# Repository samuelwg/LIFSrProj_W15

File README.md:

**Repository for Senior Project ECEn 490 Section 5, Winter 2015 Semester, BYU**

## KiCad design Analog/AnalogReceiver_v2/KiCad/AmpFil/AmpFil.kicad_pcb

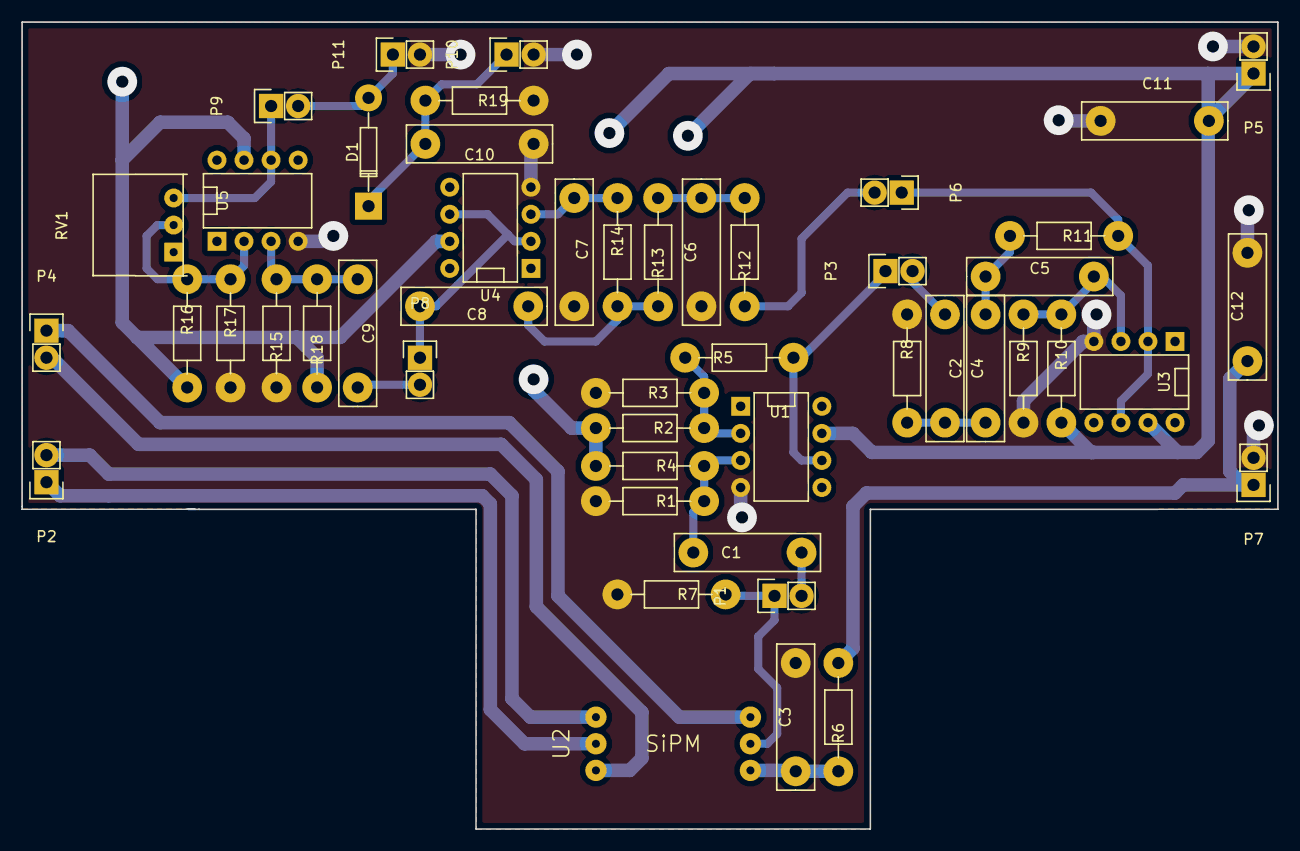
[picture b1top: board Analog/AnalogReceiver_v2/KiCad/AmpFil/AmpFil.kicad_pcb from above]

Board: 2 copper layers, 117.9 x 75.7 mm, 49 parts (0 on the bottom side), 29 nets.

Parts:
C1, C9: .2u; Cap_Horizontal_Shop
C2, C6: 22n; Cap_Horizontal_Shop
C3, C8: 10n; Cap_Horizontal_Shop
C4, C5: 33n; Cap_Horizontal_Shop
C7: 470p; Cap_Horizontal_Shop
C10: 15n; Cap_Horizontal_Shop
C11, C12: 150u; Cap_Horizontal_Shop
D1: DIODE; Diode_Shop
P1, P2, P3, P4, P5, P6, P7, P8, P9, P10, P11: CONN_01X02; Pin_Header_1x02_Shop
R1, R4, R14, R15, R18: 33k; Resistor_Horizontal_Shop
R2, R3, R16, R17: 1k; Resistor_Horizontal_Shop
R5: 12k; Resistor_Horizontal_Shop
R6: 5.6k; Resistor_Horizontal_Shop
R7: 22k; Resistor_Horizontal_Shop
R8: 4.7k; Resistor_Horizontal_Shop
R9, R10: 480k; Resistor_Horizontal_Shop
R11: 15k; Resistor_Horizontal_Shop
R12: 11k; Resistor_Horizontal_Shop
R13: 120k; Resistor_Horizontal_Shop
R19: 1meg; Resistor_Horizontal_Shop
RV1: 100-100k; Potentiometer_Shop
U1, U3, U4, U5: LT1677; DIP-8__300_Shop
U2: SiPM

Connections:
29.7V: C12.2, P7.1, R6.1
+3.3VP: C11.2, P5.1, R2.2, R4.1, R10.2, R16.2, R18.1, U1.7, U3.7, U4.7, U5.7
/A1: P3.1, R5.1, U1.6
/A2: P9.1, RV1.3, U5.6
/F1: P6.1, R11.1, U3.2, U3.6
/F2: C8.1, P8.1, U4.2, U4.6
GND: C3.1, C6.1, C7.1, C10.2, C11.1, C12.1, P5.2, P7.2, P10.2, P11.2, R1.1, R3.2, R7.2, R8.2, R9.2, R15.1, R17.2, R19.2, U1.4, U3.4, U4.4, U5.4
unnamed: C1.1, R1.2, R4.2, U1.3
unnamed: C1.2, P1.2
unnamed: C2.1, C4.2, R8.1
unnamed: C2.2, P3.2
unnamed: C3.2, R6.2, U2.6
unnamed: C4.1, C5.2, R11.2
unnamed: C5.1, R9.1, R10.1, U3.3
unnamed: C6.2, R12.1, R13.2
unnamed: C7.2, R14.1, U4.3
unnamed: C8.2, R13.1, R14.2
unnamed: C9.1, R15.2, R18.2, U5.3
unnamed: C9.2, P8.2
unnamed: P2.1, U2.2
unnamed: P2.2, U2.1
unnamed: P6.2, R12.2
unnamed: R2.1, R3.1, R5.2, U1.2
unnamed: R16.1, R17.1, RV1.2, U5.2
ThR+: P4.1, U2.4
ThR-: P4.2, U2.3
Vin: P1.1, R7.1, U2.5
Vout: D1.1, P9.2, P11.1
Voutp: C10.1, D1.2, P10.1, R19.1

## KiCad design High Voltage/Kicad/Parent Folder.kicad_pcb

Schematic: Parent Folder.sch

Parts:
C1, C2, C3, C4, C5, C6, C7, C8: C; C_1206_HandSoldering
Q1, Q2, Q3: STN0214
Q4: BUT11A; TO220_VERT
Q5: NPN; TO220_VERT
R1, R2, R3, R4, R5, R6, R7, R8, R9, R10, R11, R12, R13, R14, R15, R16, R17, R30: R; R_1206_HandSoldering
R18, R19, R20, R21, R22, R23, R24, R25, R26, R27, R28, R29: R; RES_1W
R31: Varable_Res; POT
TP1, TP2, TP3, TP4, TP5, TP6, TP7, TP8, TP9, TP10, TP11, TP12, TP13: Test_point; PINTST
U1, U2: OP275; OpAmp
U3: TEENSY3.1
U4: EMCO_F40

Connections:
+5V: R31.2; also elsewhere on the board
+12V: Q4.2 (C), U1.8 (V+), U2.8 (V+); also elsewhere on the board
-12V: U1.4 (V-), U2.4 (V-); also elsewhere on the board
GND: C1.2, C2.2, C3.2, C4.2, C5.2, C6.2, C7.2, C8.2, Q1.1 (E), Q2.1 (E), Q3.1 (E), R1.1, R2.1, R3.1, R4.1, R17.2, U3.1 (GND), U3.17 (GND), U4.2 ((-)In), U4.4 ((-)Out); also elsewhere on the board
unnamed: C1.1, R9.1, R13.2
unnamed: C2.1, R10.1, R14.2
unnamed: C3.1, R11.1, R15.2
unnamed: C4.1, R12.1, R16.2
unnamed: C5.1, Q1.3 (B), R13.1
unnamed: C6.1, Q2.3 (B), R14.1
unnamed: C7.1, Q3.3 (B), R15.1
unnamed: C8.1, Q4.1 (B), R16.1
unnamed: Q1.2 (C), Q1.4 (C), R18.2, R21.2, TP12.1
unnamed: Q2.2 (C), Q2.4 (C), R19.2, R22.2, TP9.1
unnamed: Q3.2 (C), Q3.4 (C), R20.2, R23.2, TP11.1
unnamed: Q4.3 (E), R17.1, TP5.1, U4.1 ((+)In)
unnamed: Q5.1, R30.1
unnamed: Q5.2, TP7.1
unnamed: Q5.3, R31.1
unnamed: R1.2, R5.2, U1.2 (-)
unnamed: R2.2, R6.2, U1.6 (-)
unnamed: R3.2, R7.2, U2.2 (-)
unnamed: R4.2, R8.2, U2.6 (-)
unnamed: R5.1, R9.2, TP1.1, U1.1
unnamed: R6.1, R10.2, TP2.1, U1.7
unnamed: R7.1, R11.2, TP3.1, U2.1
unnamed: R8.1, R12.2, TP4.1, U2.7
unnamed: R18.1, R24.2
unnamed: R19.1, R27.2
unnamed: R20.1, R29.2
unnamed: R21.1, R25.2
unnamed: R22.1, R26.2
unnamed: R23.1, R28.2
unnamed: R24.1, R25.1, R26.1, R27.1, R28.1, R29.1, U4.3 ((+)Out)
unnamed: R30.2, TP13.1
unnamed: TP6.1, U3.19 (DAC)
unnamed: TP8.1, U3.22 (P15)
unnamed: TP10.1, U3.21 (P14)
unnamed: U1.3 (+), U3.8 (P6)
unnamed: U1.5 (+), U3.7 (P5)
unnamed: U2.3 (+), U3.6 (P4)
unnamed: U2.5 (+), U3.5 (P3)

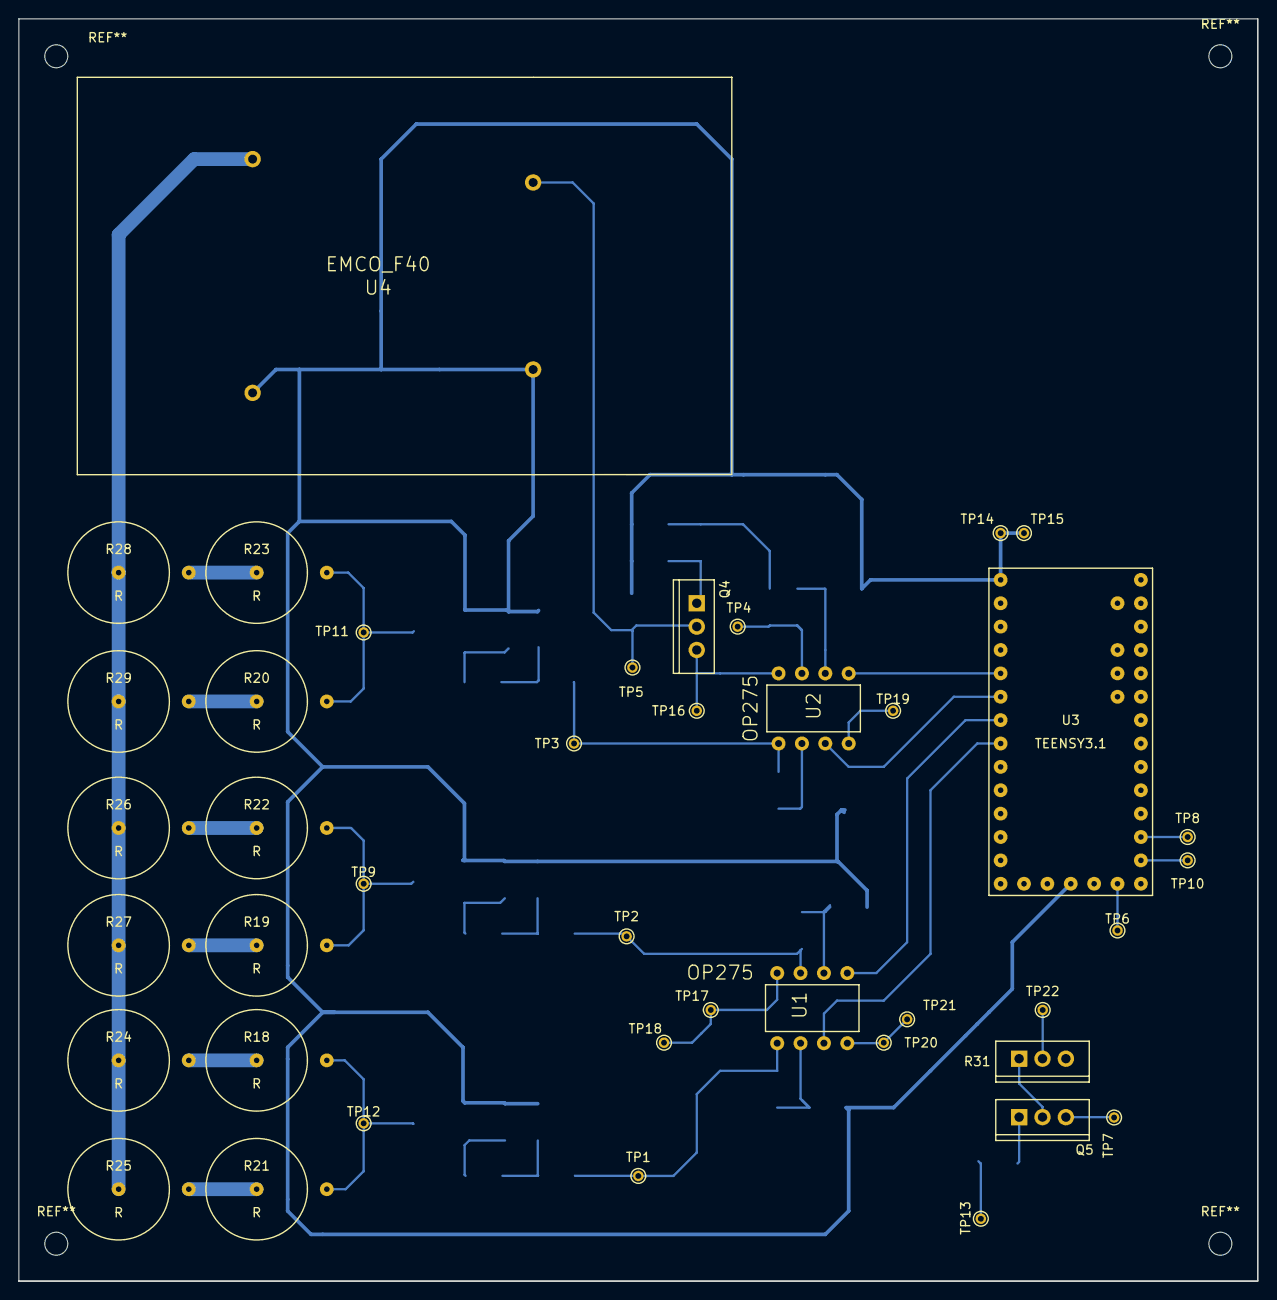
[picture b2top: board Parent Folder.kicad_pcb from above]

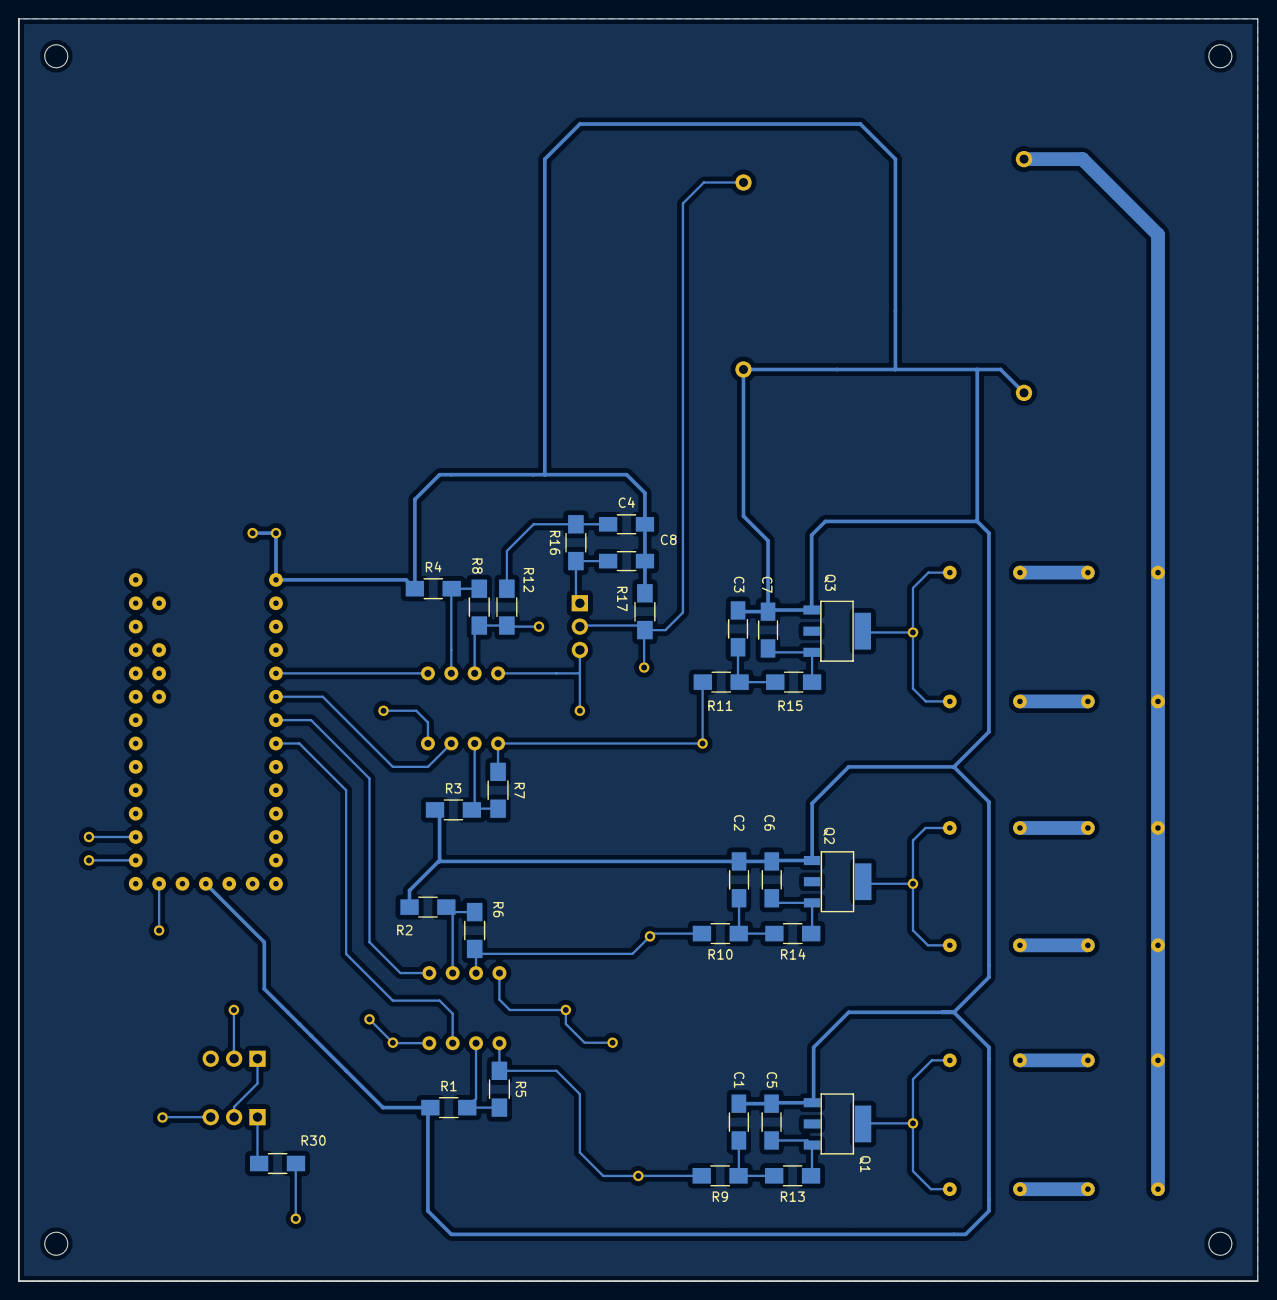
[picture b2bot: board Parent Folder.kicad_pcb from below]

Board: 2 copper layers, 134.6 x 137.2 mm, 70 parts (29 on the bottom side), 42 nets.

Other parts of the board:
TP14, TP15: GND; PINTST
TP16, TP17, TP18: +12V; PINTST
TP19, TP20, TP21: -12V; PINTST
TP22: +5V; PINTST

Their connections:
+5V: TP22.1; also elsewhere on the board
+12V: TP16.1, TP17.1, TP18.1; also elsewhere on the board
-12V: TP19.1, TP20.1, TP21.1; also elsewhere on the board
GND: TP14.1, TP15.1; also elsewhere on the board

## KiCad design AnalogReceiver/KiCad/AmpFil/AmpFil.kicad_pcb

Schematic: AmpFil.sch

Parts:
C1, C3: .2u; Capacitor13x4RM10
C2, C10: 10n; Capacitor13x4RM10
C4, C7: 22n; Capacitor13x4RM10
C5, C6: 33n; Capacitor13x4RM10
C8: 470p; Capacitor13x4RM10
C9: 15n; Capacitor13x4RM10
D1: DIODE; Diode_DO-35_SOD27_Horizontal_RM10
P1, P2, P3, P5: CONN_01X02; Pin_Header_Angled_2x01
P4: CONN_02X03; Pin_Header_Angled_2x03
P6, P7: CONN_01X02; Pin_Header_Angled_1x02
R1, R4, R8, R11, R19: 33k; Resistor_Horizontal_RM10mm
R2, R3, R9, R10: 1k; Resistor_Horizontal_RM10mm
R5: 100k; Resistor_Horizontal_RM10mm
R6: 5.6k; Resistor_Horizontal_RM10mm
R7: 22k; Resistor_Horizontal_RM10mm
R13: 4.7k; Resistor_Horizontal_RM10mm
R14, R15: 480k; Resistor_Horizontal_RM10mm
R16: 15k; Resistor_Horizontal_RM10mm
R17: 11k; Resistor_Horizontal_RM10mm
R18: 120k; Resistor_Horizontal_RM10mm
R20: 1meg; Resistor_Horizontal_RM10mm
RV1: 100-100k; Potentiometer_Trimmer-Suntan-TSR-3386C
U1: SiPM
U2, U3, U4, U5: LT1677; DIP-8__300

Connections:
29.7V: P4.6, R6.1
+3.3VP: P4.2, R2.2, R4.1, R9.2, R11.1, R15.2, U2.7 (+), U3.7 (+), U4.7 (+), U5.7 (+)
/A1: P2.1, R5.1, U2.6 (Vo)
/A2: P3.1, RV1.1, U3.6 (Vo)
/F1: P5.1, R16.1, U4.2 (-i), U4.6 (Vo)
GND: C2.1, C7.1, C8.1, C9.2, P4.1, P4.5, P6.2, P7.2, R1.1, R3.2, R7.2, R8.1, R10.2, R13.2, R14.2, R20.2, U2.4 (-), U3.4 (-), U4.4 (-), U5.4 (-)
unnamed: C1.1, R1.2, R4.2, U2.3 (+i)
unnamed: C2.2, R6.2, U1.6
unnamed: C3.1, R8.2, R11.2, U3.3 (+i)
unnamed: C3.2, P2.2
unnamed: C4.1, C5.2, R13.1
unnamed: C4.2, P3.2
unnamed: C5.1, C6.2, R16.2
unnamed: C6.1, R14.1, R15.1, U4.3 (+i)
unnamed: C7.2, R17.1, R18.2
unnamed: C8.2, R19.1, U5.3 (+i)
unnamed: C10.2, R18.1, R19.2
unnamed: P1.1, U1.2 (TE+)
unnamed: P1.2, U1.1 (TE-)
unnamed: P5.2, R17.2
unnamed: R2.1, R3.1, R5.2, U2.2 (-i)
unnamed: R9.1, R10.1, RV1.2, U3.2 (-i)
ThR+: P4.4, U1.4 (ThR)
ThR-: P4.3, U1.3 (ThR)
Vin: C1.2, R7.1, U1.5 (An(-))
Vout: C10.1, D1.1, P6.1, U5.2 (-i), U5.6 (Vo)
Voutp: C9.1, D1.2, P7.1, R20.1

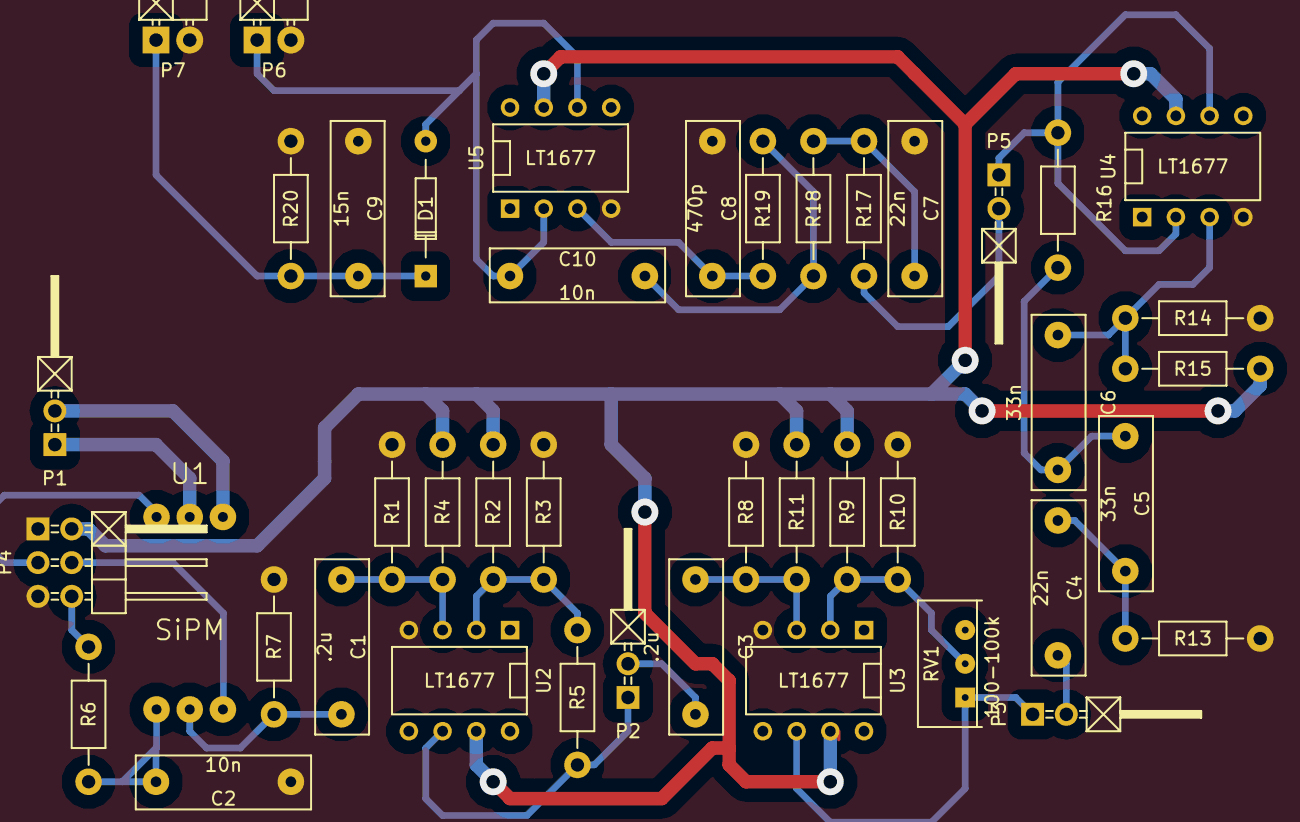
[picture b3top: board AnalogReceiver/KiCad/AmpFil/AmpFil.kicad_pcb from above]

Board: 2 copper layers, 43 parts (0 on the bottom side), 27 nets.

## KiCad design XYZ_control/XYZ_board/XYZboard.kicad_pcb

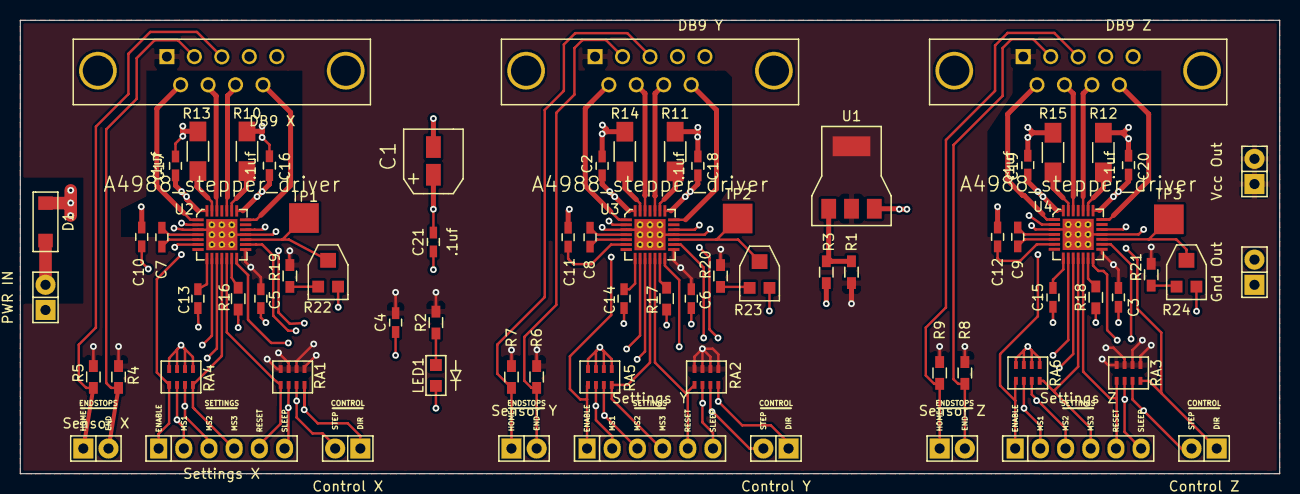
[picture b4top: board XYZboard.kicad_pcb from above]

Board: 4 copper layers, 127.0 x 45.7 mm, 75 parts (0 on the bottom side), 75 nets.

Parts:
C1: 47uF; PCE3929CT-ND
C2, C4, C5, C6, C7, C8, C9, C10, C11, C12, C16, C17, C18, C19, C20, C21: .1uf; C_0603_HandSoldering
C3: 1uF; C_0603_HandSoldering
C13, C14, C15: .22uF; C_0603_HandSoldering
D1: DIODE; SD2010S040S3R0
J1: DB9 X; DB9MD
J2: Control X; Pin_Header_Straight_1x02
J3: Control Y; Pin_Header_Straight_1x02
J4: Control Z; Pin_Header_Straight_1x02
J5: PWR IN; Pin_Header_Straight_1x02
J6: Settings X; Pin_Header_Straight_1x06
J7: Settings Y; Pin_Header_Straight_1x06
J8: Settings Z; Pin_Header_Straight_1x06
J9: Vcc Out; Pin_Header_Straight_1x02
J10: DB9 Y; DB9MD
J11: Gnd Out; Pin_Header_Straight_1x02
J12: Sensor X; Pin_Header_Straight_1x02
J13: Sensor Y; Pin_Header_Straight_1x02
J14: Sensor Z; Pin_Header_Straight_1x02
J15: DB9 Z; DB9MD
LED1: PWR LED; LGR971-KN-1
R1: 240; R_0603_HandSoldering
R2: 1k; R_0603_HandSoldering
R3, R4, R5, R6, R7, R8, R9: 715; R_0603_HandSoldering
R10, R11, R12, R13, R14, R15: .11; R_1206_HandSoldering
R16, R17, R18: 20k; R_0603_HandSoldering
R19, R20, R21: 2.49k; R_0603_HandSoldering
R22, R23, R24: 10k; TC33X-103ECT-ND
RA1, RA2, RA3, RA4, RA5, RA6: 20k; CAT16-203J4LFCT-ND
TP1, TP2, TP3: Test_point; Measurement_Point_Square-SMD-Pad_Big
U1: LM317MSTT3G_Voltage_Regulator; voltage_regulator_sot223
U2, U3, U4: A4988_stepper_driver; Qfn_28_A4988_with_thermal_vias

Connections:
GND: C1.2, C2.1, C3.1, C4.2, C5.2, C6.2, C13.1, C14.1, C15.1, C16.1, C17.1, C18.1, C19.1, C20.1, C21.1, J1.4, J5.1, J10.4, J11.1, J11.2, J15.4, LED1.2, R3.1, R10.1, R11.1, R12.1, R13.1, R14.1, R15.1, R16.1, R17.1, R18.1, R22.3, R23.3, R24.3, RA4.1, RA4.2, RA4.3, RA4.4, RA5.1, RA5.2, RA5.3, RA5.4, RA6.1, RA6.2, RA6.3, RA6.4, U2.3, U2.18, U2.29, U3.3, U3.18, U3.29, U4.3, U4.18, U4.29
unnamed: C7.1, U2.4
unnamed: C7.2, U2.5
unnamed: C8.1, U3.4
unnamed: C8.2, U3.5
unnamed: C9.1, U4.4
unnamed: C9.2, U4.5
unnamed: C10.2, U2.6
unnamed: C11.2, U3.6
unnamed: C12.2, U4.6
unnamed: C13.2, U2.8
unnamed: C14.2, U3.8
unnamed: C15.2, U4.8
unnamed: LED1.1, R2.1
unnamed: R1.1, R3.2, U1.1
unnamed: R10.2, U2.23
unnamed: R11.2, U3.23
unnamed: R12.2, U4.23
unnamed: R13.2, U2.27
unnamed: R14.2, U3.27
unnamed: R15.2, U4.27
unnamed: R16.2, U2.13
unnamed: R17.2, U3.13
unnamed: R18.2, U4.13
unnamed: R19.1, R22.1
unnamed: R20.1, R23.1
unnamed: R21.1, R24.1
PWR_IN: D1.1, J5.2
V+: C1.1, C2.2, C10.1, C11.1, C12.1, C16.2, C17.2, C18.2, C19.2, C20.2, C21.2, D1.2, U1.3, U2.22, U2.28, U3.22, U3.28, U4.22, U4.28
VCC: C3.2, C4.1, C5.1, C6.1, J1.1, J9.1, J9.2, J10.1, J15.1, R1.2, R2.2, R4.2, R5.2, R6.2, R7.2, R8.2, R9.2, R19.2, R20.2, R21.2, RA1.5, RA1.6, RA1.7, RA1.8, RA2.5, RA2.6, RA2.7, RA2.8, RA3.5, RA3.6, RA3.7, RA3.8, U1.2, U1.4, U2.15, U3.15, U4.15
dir1: J2.1, RA1.4, U2.19
dir2: J3.1, RA2.4, U3.19
dir3: J4.1, RA3.4, U4.19
enable1: J6.1, RA4.5, U2.2
enable2: J7.1, RA5.5, U3.2
enable3: J8.1, RA6.5, U4.2
ms1_1: J6.2, RA4.6, U2.9
ms1_2: J7.2, RA5.6, U3.9
ms1_3: J8.2, RA6.6, U4.9
ms2_1: J6.3, RA4.7, U2.10
ms2_2: J7.3, RA5.7, U3.10
ms2_3: J8.3, RA6.7, U4.10
ms3_1: J6.4, RA4.8, U2.11
ms3_2: J7.4, RA5.8, U3.11
ms3_3: J8.4, RA6.8, U4.11
out1a_1: J1.8, U2.24
out1a_2: J10.8, U3.24
out1a_3: J15.8, U4.24
out1b_1: J1.9, U2.21
out1b_2: J10.9, U3.21
out1b_3: J15.9, U4.21
out2a_1: J1.7, U2.26
out2a_2: J10.7, U3.26
out2a_3: J15.7, U4.26
out2b_1: J1.6, U2.1
out2b_2: J10.6, U3.1
out2b_3: J15.6, U4.1
ref1: R22.2, TP1.1, U2.17
ref2: R23.2, TP2.1, U3.17
ref3: R24.2, TP3.1, U4.17
reset1: J6.5, RA1.1, U2.12
reset2: J7.5, RA2.1, U3.12
reset3: J8.5, RA3.1, U4.12
sensor1_1: J1.2, J12.2, R4.1
sensor1_2: J10.2, J13.2, R6.1
sensor1_3: J14.2, J15.2, R8.1
sensor2_1: J1.3, J12.1, R5.1
sensor2_2: J10.3, J13.1, R7.1
sensor2_3: J14.1, J15.3, R9.1
sleep1: J6.6, RA1.2, U2.14
sleep2: J7.6, RA2.2, U3.14
sleep3: J8.6, RA3.2, U4.14
step1: J2.2, RA1.3, U2.16
step2: J3.2, RA2.3, U3.16
step3: J4.2, RA3.3, U4.16

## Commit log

2015-01-22 adding XYZ control code
2015-01-26 Adding XYZ motor control board design
2015-01-27 Updated motor control board
    Added pull up resistors for the hall effect sensors
2015-01-27 updated motor control footprints
2015-01-27 Worked on python interface for XYZ
2015-01-27 removed hidden folder
2015-01-28 Added pcb file and footprint lib
2015-01-28 Added footprints
    added footprints for db9 connector and the qfn stepper driver
2015-01-28 Added Schematic
    I added a schematic and folder for the analog filter portion of the
    project.
2015-01-31 updated resistor values
2015-01-31 Updated parts on board
2015-01-31 updated the bill of materials
2015-02-01 updated BOM
2015-02-03 voltage regulator footprint and association
2015-02-03 board update
2015-02-06 Schematics
    With this commit I’ve added all the circuit schematics made up to this
    point. This is mainly just the schematic files for the amplifier/filter
    circuit.
2015-02-07 Adjusted pinout to processor
    rearranged pinout for pins to processor. Removed individual grounds for
    each set. Added vcc and gnd out
2015-02-07 Replaced pull-up and pull-down
    Replaced 20k pull up and pull down resistors with resistor arrays. Also
    reannotated the board and updated the BOM
2015-02-07 Started board layout
2015-02-09 added Arduino receiver
2015-02-11 Create test
2015-02-11 KiCad Schematics Upload
    This is just the KiCad files that I’m uploading right now.
2015-02-11 debuged arduino reciever
2015-02-13 Added code for PWM on the Teensy
2015-02-13 Organized the code and added explanatory comments.
2015-02-13 More comments
2015-02-14 xyz board progress
2015-02-16 Current Clamping Design
    Printed and tested. Works!
2015-02-20 Modified Testing Adapter
    Still unprinted or tested
2015-02-20 Parts and STL Files
    No new changes
2015-02-20 Added TeensyUI
2015-02-20 Updated the board and added output files
2015-02-21 New Work on PCB
    I did a lot of work and development on the PCB for the
    amplifier/filter. There should be a bunch of new files and
    modifications.
2015-02-21 Added Power Supply housing model
2015-02-23 Deleted Files
    I removed files to help maybe fix a problem with Github syncing.
2015-02-23 Last changes
    I made some last changes to the PCB, mainly bias.
2015-02-23 Re-added Files
    I re-added the files to hopefully get everything up and bypass the
    syncing problem I was having.
2015-02-23 Update on Teensy PWM control
2015-02-24 Minor changes to fit actual ND Filter
    This is what was printed
2015-02-25 Serial commands added.
2015-02-27 Teensy footprint, schematic for HV system
2015-02-27 Testing 2/27/2015
2015-03-02 Updated TeensyUI
2015-03-02 Added .ino file to Teensy Data
2015-03-02 Added sample output file to TeensyUI
2015-03-04 Updated TeensyUI Files
2015-03-13 Loading characterization & other comments
2015-03-13 Characterized flowing configuration
2015-03-13 PWM1
2015-03-13 actually pwm1
2015-03-16 Some Changes
    I made some minor changes.
2015-03-16 Updated Teensy Files
2015-03-18 High voltage schematic changes
2015-03-18 Updating My Work
    I’ve done a lot of work with making a new filter board. It’s all here.
2015-03-18 add .gitignore file
2015-03-25 teensyui update
2015-03-25 HV schematic and layout
2015-03-25 New Cutoffs
    I tweaked the designs to give different cutoff frequencies and ripple
    levels.
2015-03-26 Made a few changes to the board. I think it's ready to be milled
2015-03-27 Updated teensy python code
2015-03-27 Files Made
    I made some files in trying to export this Kicad stuff to Eagle.
2015-03-29 More teensy python changes
2015-03-30 Additional changes to the board, drill files, etc
2015-04-01 Updated teensy code, added recorded data plotter
2015-04-01 Data & plots from trying HV system with Chemistry LIF setup
2015-04-01 Plot data from HV test at Chemistry on 3-30-15
2015-04-03 Updated data file
2015-04-06 updated graphing method and variable names
2015-04-10 Design Changes
    I made some design changes to shift the cutoff frequencies.
2015-04-10 Updating Files
    Making sure all files are up to date for the project documentation.
2015-04-12 updated code. added comments to code
2015-04-13 look at data with simple matplotlib
2015-04-15 Uploading Files
    I’ve uploaded files that were important to testing the board.
